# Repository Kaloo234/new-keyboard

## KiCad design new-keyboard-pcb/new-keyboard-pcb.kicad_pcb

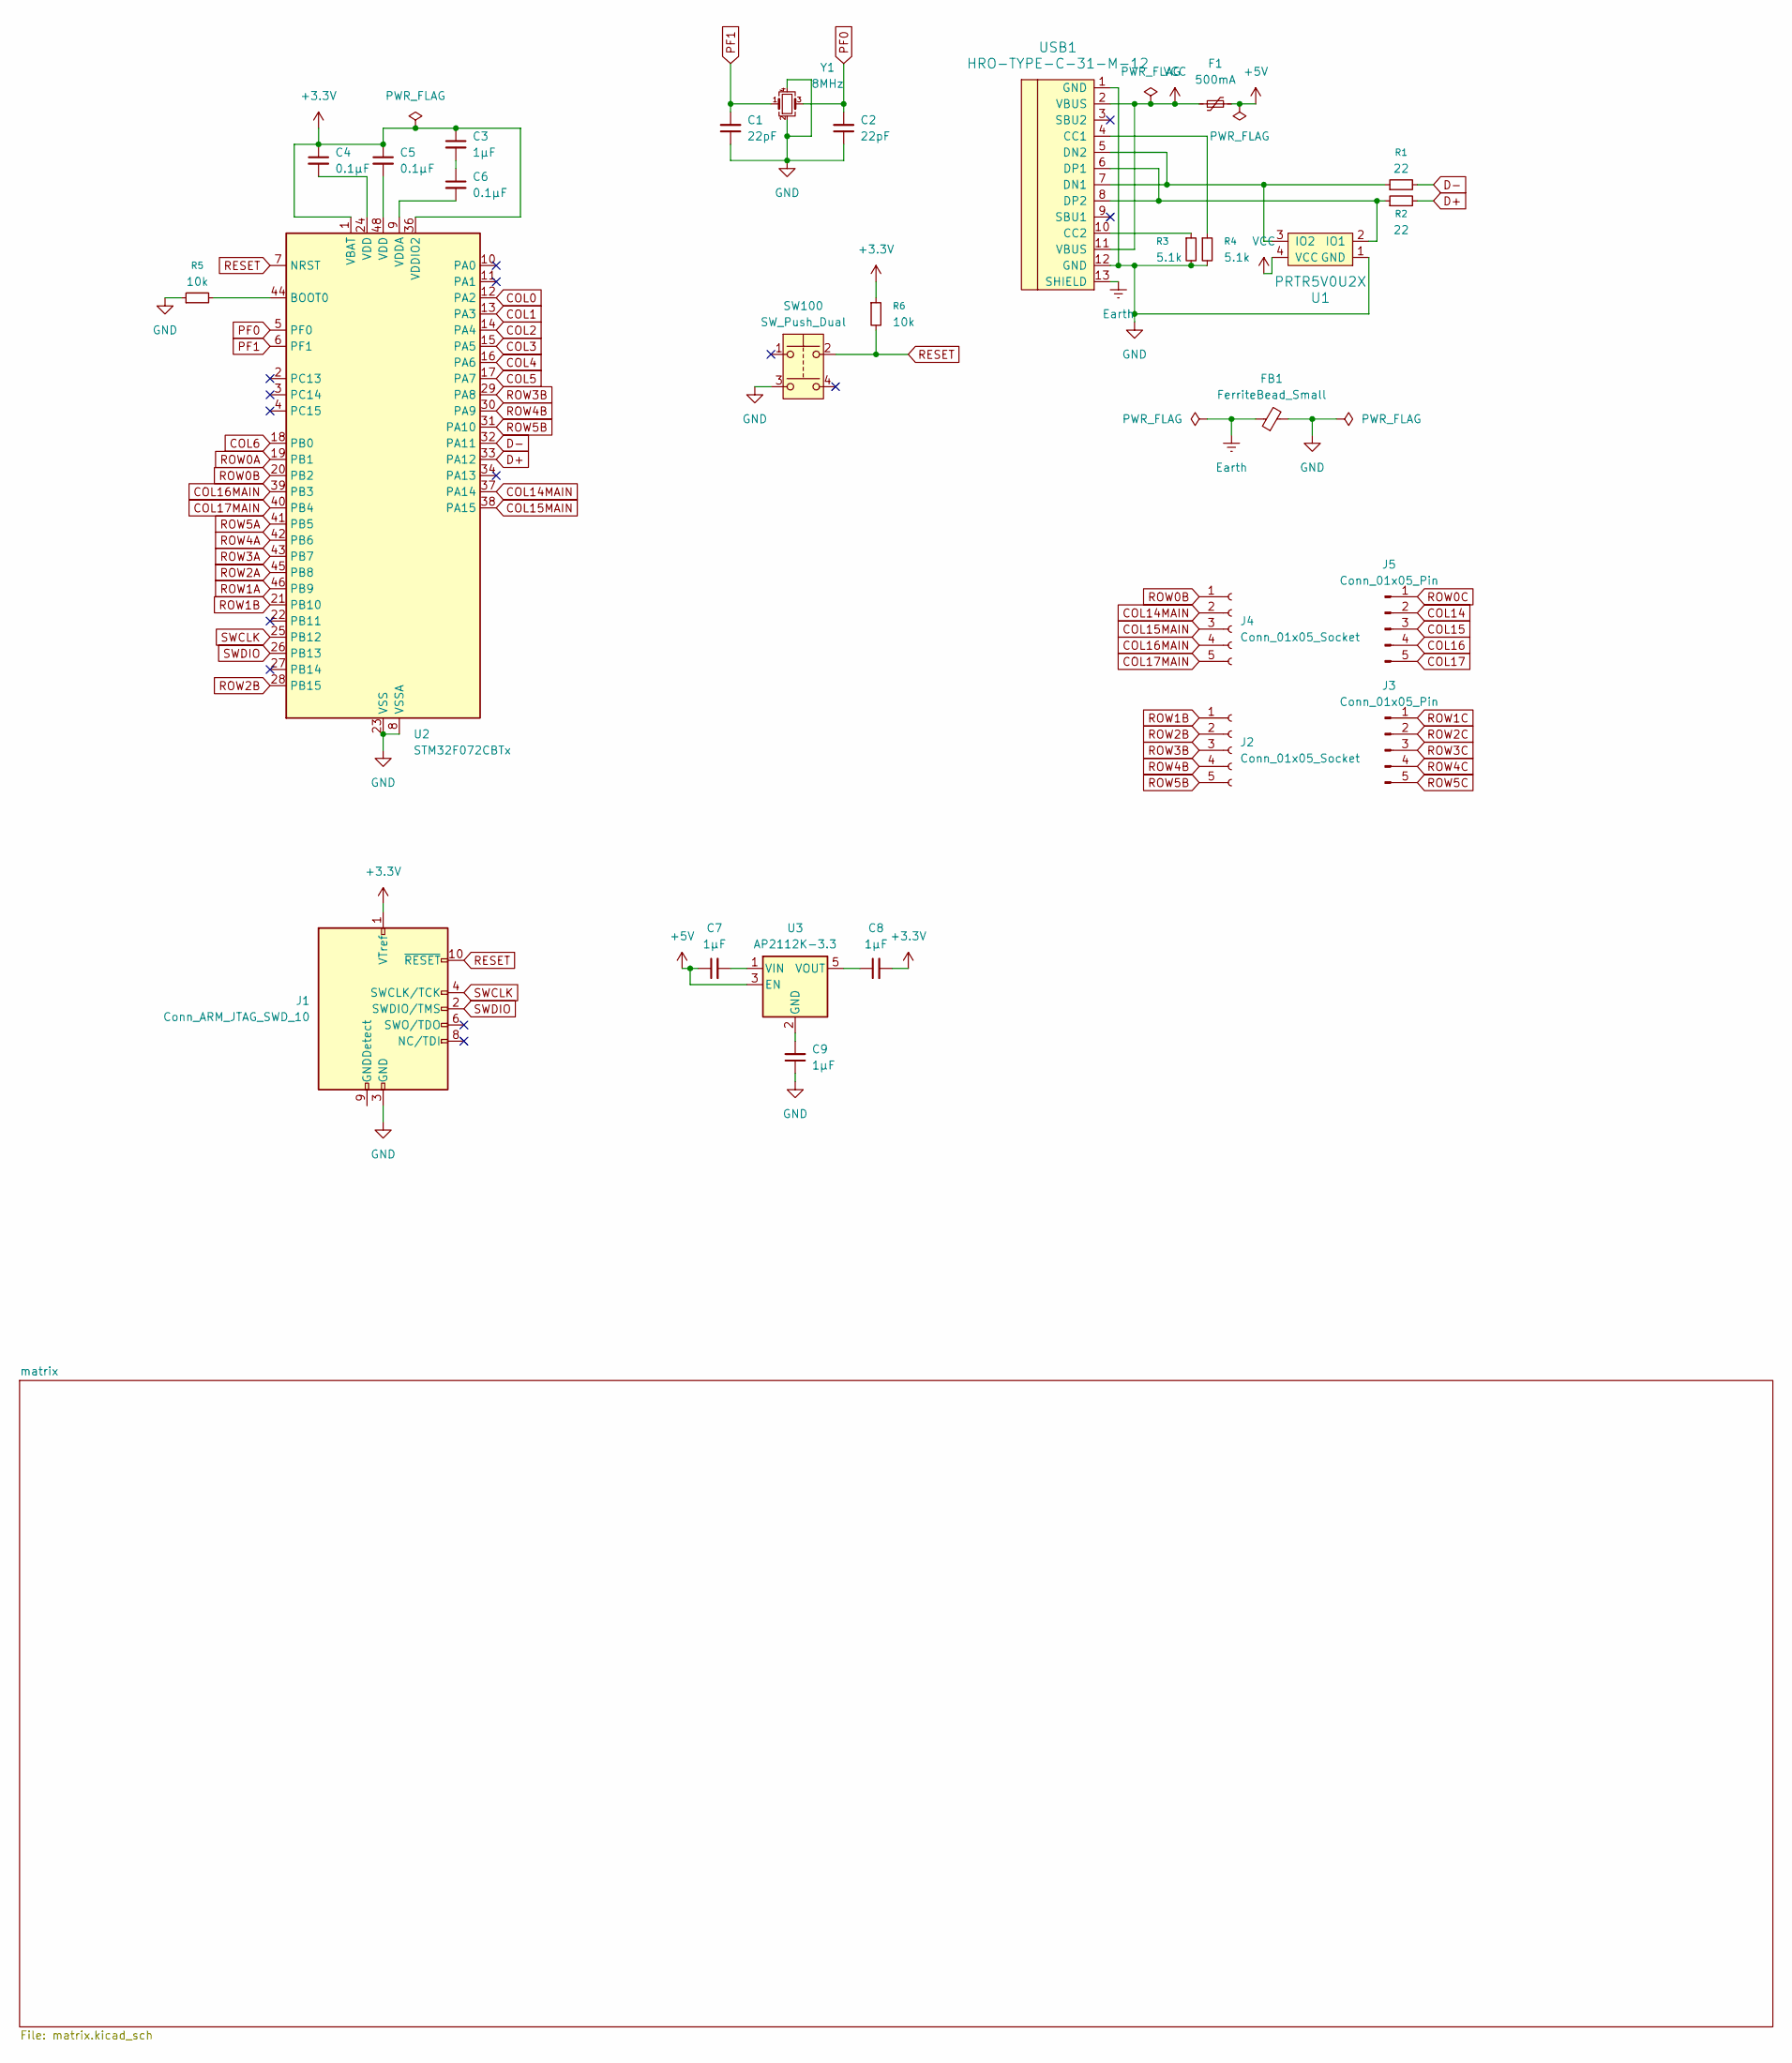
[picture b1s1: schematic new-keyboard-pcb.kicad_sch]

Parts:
C1, C2: 22pF; C_0805_2012Metric_Pad1.18x1.45mm_HandSolder
C3, C7, C8, C9: 1µF; C_0805_2012Metric_Pad1.18x1.45mm_HandSolder
C4, C5, C6: 0.1µF; C_0805_2012Metric_Pad1.18x1.45mm_HandSolder
F1: 500mA; Fuse_1206_3216Metric_Pad1.42x1.75mm_HandSolder
FB1: FerriteBead_Small; L_0805_2012Metric_Pad1.05x1.20mm_HandSolder
J1: Conn_ARM_JTAG_SWD_10; PinSocket_2x05_P2.54mm_Vertical
J2, J4: Conn_01x05_Socket; connector
J3, J5: Conn_01x05_Pin; connector
R1, R2: 22; R_0805_2012Metric_Pad1.20x1.40mm_HandSolder
R3, R4: 5.1k; R_0805_2012Metric_Pad1.20x1.40mm_HandSolder
R5, R6: 10k; R_0805_2012Metric_Pad1.20x1.40mm_HandSolder
SW100: SW_Push_Dual; SKQG-1155865
U1: PRTR5V0U2X; SOT143B
U2: STM32F072CBTx; LQFP-48_7x7mm_P0.5mm
U3: AP2112K-3.3; SOT-23-5
USB1: HRO-TYPE-C-31-M-12; HRO-TYPE-C-31-M-12-HandSoldering
Y1: 8MHz; Crystal_SMD_3225-4Pin_3.2x2.5mm_HandSoldering

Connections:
+3.3V: C3.1, C4.1, C5.1, C8.2, J1.1 (VTref), R6.1, U2.1 (VBAT), U2.36 (VDDIO2)
+5V: C7.1, F1.2, U3.3 (EN)
COL0: U2.12 (PA2); also elsewhere on the board
COL1: U2.13 (PA3); also elsewhere on the board
COL2: U2.14 (PA4); also elsewhere on the board
COL3: U2.15 (PA5); also elsewhere on the board
COL4: U2.16 (PA6); also elsewhere on the board
COL5: U2.17 (PA7); also elsewhere on the board
COL6: U2.18 (PB0); also elsewhere on the board
COL14: J5.2; also elsewhere on the board
COL14MAIN: J4.2, U2.37 (PA14)
COL15: J5.3; also elsewhere on the board
COL15MAIN: J4.3, U2.38 (PA15)
COL16: J5.4; also elsewhere on the board
COL16MAIN: J4.4, U2.39 (PB3)
COL17: J5.5; also elsewhere on the board
COL17MAIN: J4.5, U2.40 (PB4)
D+: R2.2, U2.33 (PA12)
D-: R1.2, U2.32 (PA11)
Earth: FB1.1, USB1.13 (SHIELD)
GND: C1.1, C2.1, C9.1, FB1.2, J1.3 (GND), J1.5 (GND), R3.2, R4.2, R5.1, SW100.3, U1.1 (GND), U2.8 (VSSA), U2.23 (VSS), U2.35 (VSS), U2.47 (VSS), USB1.1 (GND), USB1.12 (GND), Y1.2, Y1.4
unnamed: C3.2, C6.1
unnamed: C4.2, U2.24 (VDD)
unnamed: C5.2, U2.48 (VDD)
unnamed: R2.1, U1.2 (IO1), USB1.6 (DP1), USB1.8 (DP2)
unnamed: R1.1, U1.3 (IO2), USB1.5 (DN2), USB1.7 (DN1)
unnamed: R5.2, U2.44 (BOOT0)
unnamed: C6.2, U2.9 (VDDA)
unnamed: C9.2, U3.2 (GND)
unnamed: C7.2, U3.1 (VIN)
unnamed: C8.1, U3.5 (VOUT)
unnamed: R4.1, USB1.4 (CC1)
unnamed: R3.1, USB1.10 (CC2)
PF0: C2.2, U2.5 (PF0), Y1.3
PF1: C1.2, U2.6 (PF1), Y1.1
RESET: J1.10 (~RESET), R6.2, SW100.2, U2.7 (NRST)
ROW0A: U2.19 (PB1); also elsewhere on the board
ROW0B: J4.1, U2.20 (PB2); also elsewhere on the board
ROW0C: J5.1; also elsewhere on the board
ROW1A: U2.46 (PB9); also elsewhere on the board
ROW1B: J2.1, U2.21 (PB10); also elsewhere on the board
ROW1C: J3.1; also elsewhere on the board
ROW2A: U2.45 (PB8); also elsewhere on the board
ROW2B: J2.2, U2.28 (PB15); also elsewhere on the board
ROW2C: J3.2; also elsewhere on the board
ROW3A: U2.43 (PB7); also elsewhere on the board
ROW3B: J2.3, U2.29 (PA8); also elsewhere on the board
ROW3C: J3.3; also elsewhere on the board
ROW4A: U2.42 (PB6); also elsewhere on the board
ROW4B: J2.4, U2.30 (PA9); also elsewhere on the board
ROW4C: J3.4; also elsewhere on the board
ROW5A: U2.41 (PB5); also elsewhere on the board
ROW5B: J2.5, U2.31 (PA10); also elsewhere on the board
ROW5C: J3.5; also elsewhere on the board
SWCLK: J1.4 (SWCLK/TCK), U2.25 (PB12)
SWDIO: J1.2 (SWDIO/TMS), U2.26 (PB13)
VCC: F1.1, U1.4 (VCC), USB1.2 (VBUS), USB1.11 (VBUS)

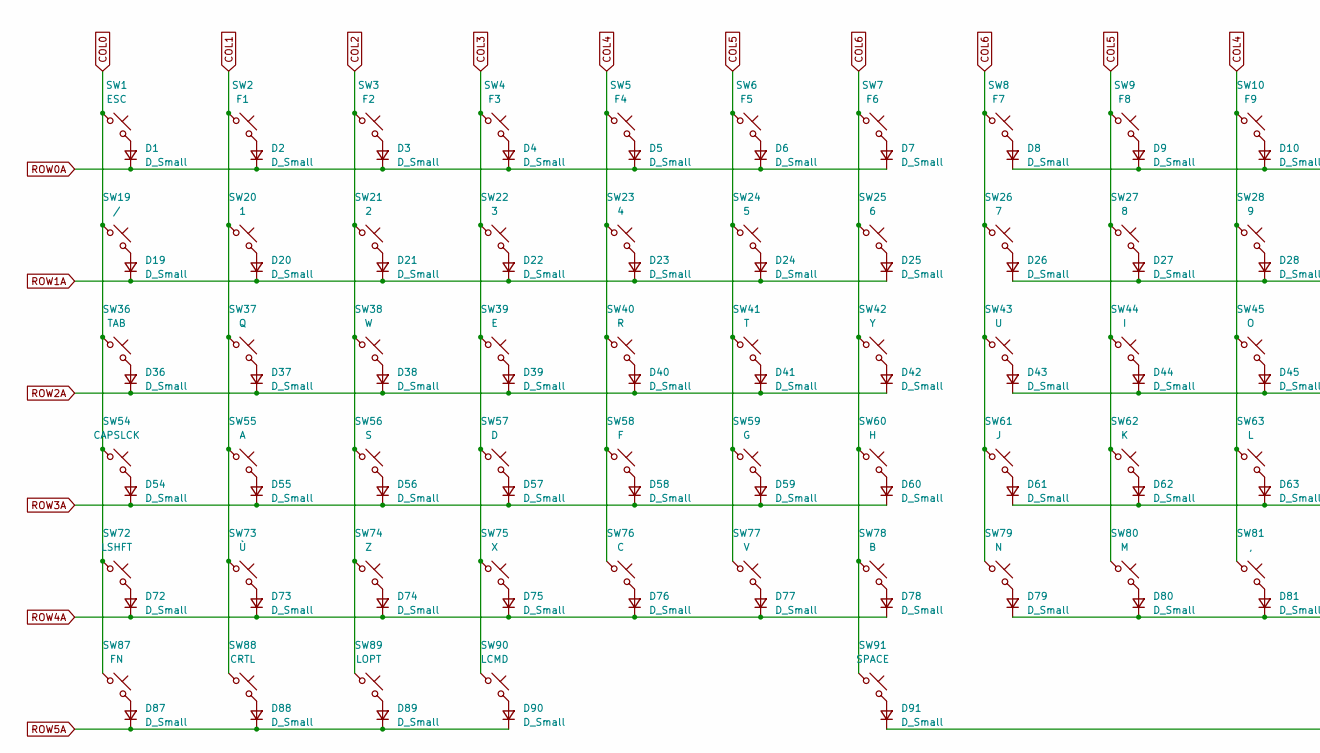
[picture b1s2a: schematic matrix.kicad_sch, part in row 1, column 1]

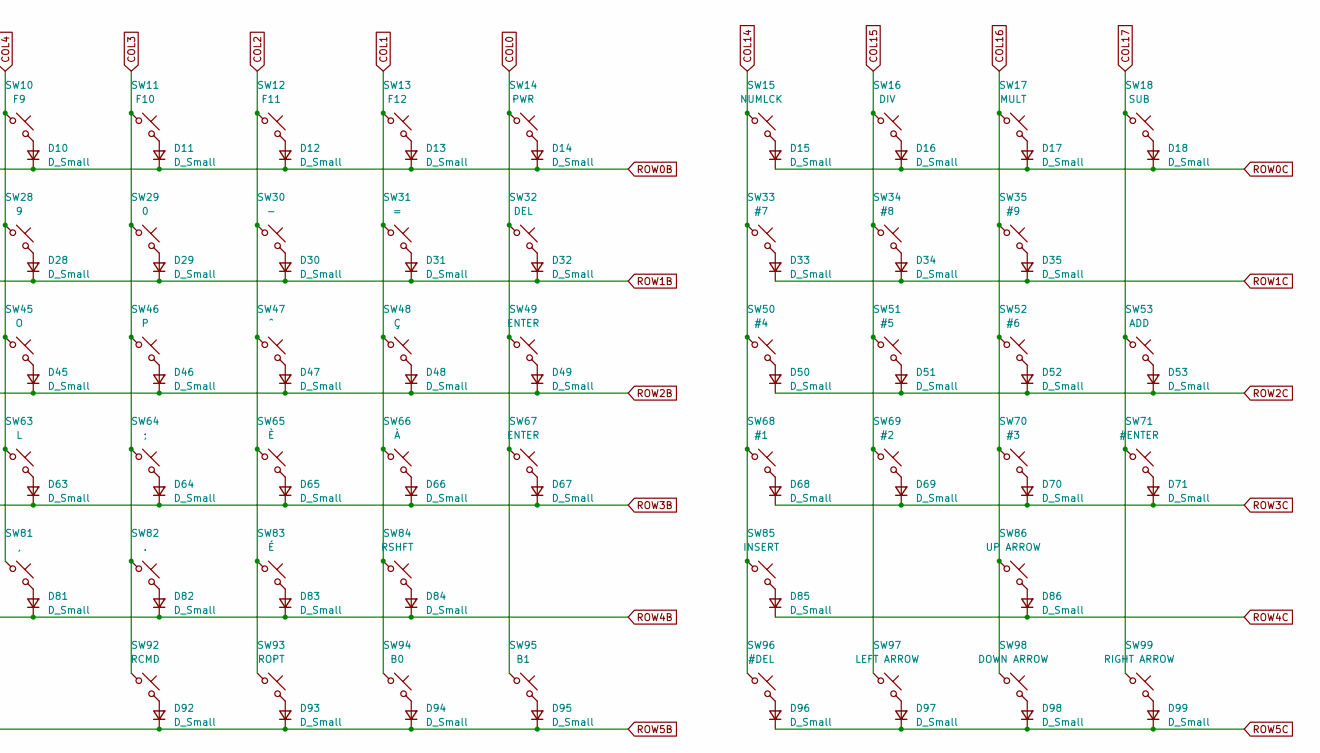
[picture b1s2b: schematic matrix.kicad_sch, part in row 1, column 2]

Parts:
D1, D2, D3, D4, D5, D6, D7, D8, D9, D10, D11, D12, D13, D14, D15, D16, D17, D18, D19, D20, D21, D22, D23, D24, D25, D26, D27, D28, D29, D30, D31, D32, D33, D34, D35, D36, D37, D38, D39, D40, D41, D42, D43, D44, D45, D46, D47, D48, D49, D50, D51, D52, D53, D54, D55, D56, D57, D58, D59, D60, D61, D62, D63, D64, D65, D66, D67, D68, D69, D70, D71, D72, D73, D74, D75, D76, D77, D78, D79, D80, D81, D82, D83, D84, D85, D86, D87, D88, D89, D90, D91, D92, D93, D94, D95, D96, D97, D98, D99: D_Small; D_0805_2012Metric_Pad1.15x1.40mm_HandSolder
SW1: ESC; Kailh-PG1353-Hotswap-1.5U
SW2: F1; Kailh-PG1353-Hotswap-1U
SW3: F2; Kailh-PG1353-Hotswap-1U
SW4: F3; Kailh-PG1353-Hotswap-1U
SW5: F4; Kailh-PG1353-Hotswap-1U
SW6: F5; Kailh-PG1353-Hotswap-1U
SW7: F6; Kailh-PG1353-Hotswap-1U
SW8: F7; Kailh-PG1353-Hotswap-1U
SW9: F8; Kailh-PG1353-Hotswap-1U
SW10: F9; Kailh-PG1353-Hotswap-1U
SW11: F10; Kailh-PG1353-Hotswap-1U
SW12: F11; Kailh-PG1353-Hotswap-1U
SW13: F12; Kailh-PG1353-Hotswap-1U
SW14: PWR; Kailh-PG1353-Hotswap-1.5U
SW15: NUMLCK; Kailh-PG1353-Hotswap-1U
SW16: DIV; Kailh-PG1353-Hotswap-1U
SW17: MULT; Kailh-PG1353-Hotswap-1U
SW18: SUB; Kailh-PG1353-Hotswap-1U
SW19: /; Kailh-PG1353-Hotswap-1U
SW20: 1; Kailh-PG1353-Hotswap-1U
SW21: 2; Kailh-PG1353-Hotswap-1U
SW22: 3; Kailh-PG1353-Hotswap-1U
SW23: 4; Kailh-PG1353-Hotswap-1U
SW24: 5; Kailh-PG1353-Hotswap-1U
SW25: 6; Kailh-PG1353-Hotswap-1U
SW26: 7; Kailh-PG1353-Hotswap-1U
SW27: 8; Kailh-PG1353-Hotswap-1U
SW28: 9; Kailh-PG1353-Hotswap-1U
SW29: 0; Kailh-PG1353-Hotswap-1U
SW30: -; Kailh-PG1353-Hotswap-1U
SW31: =; Kailh-PG1353-Hotswap-1U
SW32: DEL; Kailh-PG1353-Hotswap-2U
SW33: #7; Kailh-PG1353-Hotswap-1U
SW34: #8; Kailh-PG1353-Hotswap-1U
SW35: #9; Kailh-PG1353-Hotswap-1U
SW36: TAB; Kailh-PG1353-Hotswap-1.5U
SW37: Q; Kailh-PG1353-Hotswap-1U
SW38: W; Kailh-PG1353-Hotswap-1U
SW39: E; Kailh-PG1353-Hotswap-1U
SW40: R; Kailh-PG1353-Hotswap-1U
SW41: T; Kailh-PG1353-Hotswap-1U
SW42: Y; Kailh-PG1353-Hotswap-1U
SW43: U; Kailh-PG1353-Hotswap-1U
SW44: I; Kailh-PG1353-Hotswap-1U
SW45: O; Kailh-PG1353-Hotswap-1U
SW46: P; Kailh-PG1353-Hotswap-1U
SW47: ^; Kailh-PG1353-Hotswap-1U
SW48: Ç; Kailh-PG1353-Hotswap-1U
SW49: ENTER; Kailh-PG1353-Hotswap-1.5U
SW50: #4; Kailh-PG1353-Hotswap-1U
SW51: #5; Kailh-PG1353-Hotswap-1U
SW52: #6; Kailh-PG1353-Hotswap-1U
SW53: ADD; Kailh-PG1353-Hotswap-2U
SW54: CAPSLCK; Kailh-PG1353-Hotswap-1.75U
SW55: A; Kailh-PG1353-Hotswap-1U
SW56: S; Kailh-PG1353-Hotswap-1U
SW57: D; Kailh-PG1353-Hotswap-1U
SW58: F; Kailh-PG1353-Hotswap-1U
SW59: G; Kailh-PG1353-Hotswap-1U
SW60: H; Kailh-PG1353-Hotswap-1U
SW61: J; Kailh-PG1353-Hotswap-1U
SW62: K; Kailh-PG1353-Hotswap-1U
SW63: L; Kailh-PG1353-Hotswap-1U
SW64: ;; Kailh-PG1353-Hotswap-1U
SW65: È; Kailh-PG1353-Hotswap-1U
SW66: À; Kailh-PG1353-Hotswap-1U
SW67: ENTER; Kailh-PG1353-Hotswap-1.25U
SW68: #1; Kailh-PG1353-Hotswap-1U
SW69: #2; Kailh-PG1353-Hotswap-1U
SW70: #3; Kailh-PG1353-Hotswap-1U
SW71: #ENTER; Kailh-PG1353-Hotswap-2U
SW72: LSHFT; Kailh-PG1353-Hotswap-1.25U
SW73: Ù; Kailh-PG1353-Hotswap-1U
SW74: Z; Kailh-PG1353-Hotswap-1U
SW75: X; Kailh-PG1353-Hotswap-1U
SW76: C; Kailh-PG1353-Hotswap-1U
SW77: V; Kailh-PG1353-Hotswap-1U
SW78: B; Kailh-PG1353-Hotswap-1U
SW79: N; Kailh-PG1353-Hotswap-1U
SW80: M; Kailh-PG1353-Hotswap-1U
SW81: ,; Kailh-PG1353-Hotswap-1U
SW82: .; Kailh-PG1353-Hotswap-1U
SW83: É; Kailh-PG1353-Hotswap-1U
SW84: RSHFT; Kailh-PG1353-Hotswap-2.75U
SW85: INSERT; Kailh-PG1353-Hotswap-2U
SW86: UP ARROW; Kailh-PG1353-Hotswap-1U
SW87: FN; Kailh-PG1353-Hotswap-1U
SW88: CRTL; Kailh-PG1353-Hotswap-1U
SW89: LOPT; Kailh-PG1353-Hotswap-1U
SW90: LCMD; Kailh-PG1353-Hotswap-1.25U
SW91: SPACE; Kailh-PG1353-Hotswap-6.25U
SW92: RCMD; Kailh-PG1353-Hotswap-1.25U
SW93: ROPT; Kailh-PG1353-Hotswap-1U
SW94: B0; Kailh-PG1353-Hotswap-1.25U
SW95: B1; Kailh-PG1353-Hotswap-1U
SW96: #DEL; Kailh-PG1353-Hotswap-1U
SW97: LEFT ARROW; Kailh-PG1353-Hotswap-1U
SW98: DOWN ARROW; Kailh-PG1353-Hotswap-1U
SW99: RIGHT ARROW; Kailh-PG1353-Hotswap-1U

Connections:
COL0: SW1.1, SW14.1, SW19.1, SW32.1, SW36.1, SW49.1, SW54.1, SW67.1, SW72.1, SW87.1, SW95.1; also elsewhere on the board
COL1: SW2.1, SW13.1, SW20.1, SW31.1, SW37.1, SW48.1, SW55.1, SW66.1, SW73.1, SW84.1, SW88.1, SW94.1; also elsewhere on the board
COL2: SW3.1, SW12.1, SW21.1, SW30.1, SW38.1, SW47.1, SW56.1, SW65.1, SW74.1, SW83.1, SW89.1, SW93.1; also elsewhere on the board
COL3: SW4.1, SW11.1, SW22.1, SW29.1, SW39.1, SW46.1, SW57.1, SW64.1, SW75.1, SW82.1, SW90.1, SW92.1; also elsewhere on the board
COL4: SW5.1, SW10.1, SW23.1, SW28.1, SW40.1, SW45.1, SW58.1, SW63.1, SW76.1, SW81.1; also elsewhere on the board
COL5: SW6.1, SW9.1, SW24.1, SW27.1, SW41.1, SW44.1, SW59.1, SW62.1, SW77.1, SW80.1; also elsewhere on the board
COL6: SW7.1, SW8.1, SW25.1, SW26.1, SW42.1, SW43.1, SW60.1, SW61.1, SW78.1, SW79.1, SW91.1; also elsewhere on the board
COL14: SW15.1, SW33.1, SW50.1, SW68.1, SW85.1, SW96.1; also elsewhere on the board
COL15: SW16.1, SW34.1, SW51.1, SW69.1, SW97.1; also elsewhere on the board
COL16: SW17.1, SW35.1, SW52.1, SW70.1, SW86.1, SW98.1; also elsewhere on the board
COL17: SW18.1, SW53.1, SW71.1, SW99.1; also elsewhere on the board
unnamed: D1.2 (A), SW1.2
unnamed: D2.2 (A), SW2.2
unnamed: D3.2 (A), SW3.2
unnamed: D4.2 (A), SW4.2
unnamed: D5.2 (A), SW5.2
unnamed: D6.2 (A), SW6.2
unnamed: D7.2 (A), SW7.2
unnamed: D8.2 (A), SW8.2
unnamed: D9.2 (A), SW9.2
unnamed: D10.2 (A), SW10.2
unnamed: D11.2 (A), SW11.2
unnamed: D12.2 (A), SW12.2
unnamed: D13.2 (A), SW13.2
unnamed: D14.2 (A), SW14.2
unnamed: D15.2 (A), SW15.2
unnamed: D16.2 (A), SW16.2
unnamed: D17.2 (A), SW17.2
unnamed: D18.2 (A), SW18.2
unnamed: D19.2 (A), SW19.2
unnamed: D20.2 (A), SW20.2
unnamed: D21.2 (A), SW21.2
unnamed: D22.2 (A), SW22.2
unnamed: D23.2 (A), SW23.2
unnamed: D24.2 (A), SW24.2
unnamed: D25.2 (A), SW25.2
unnamed: D26.2 (A), SW26.2
unnamed: D27.2 (A), SW27.2
unnamed: D28.2 (A), SW28.2
unnamed: D29.2 (A), SW29.2
unnamed: D30.2 (A), SW30.2
unnamed: D31.2 (A), SW31.2
unnamed: D32.2 (A), SW32.2
unnamed: D33.2 (A), SW33.2
unnamed: D34.2 (A), SW34.2
unnamed: D35.2 (A), SW35.2
unnamed: D36.2 (A), SW36.2
unnamed: D37.2 (A), SW37.2
unnamed: D38.2 (A), SW38.2
unnamed: D39.2 (A), SW39.2
unnamed: D40.2 (A), SW40.2
unnamed: D41.2 (A), SW41.2
unnamed: D42.2 (A), SW42.2
unnamed: D43.2 (A), SW43.2
unnamed: D44.2 (A), SW44.2
unnamed: D45.2 (A), SW45.2
unnamed: D46.2 (A), SW46.2
unnamed: D47.2 (A), SW47.2
unnamed: D48.2 (A), SW48.2
unnamed: D49.2 (A), SW49.2
unnamed: D50.2 (A), SW50.2
unnamed: D51.2 (A), SW51.2
unnamed: D52.2 (A), SW52.2
unnamed: D53.2 (A), SW53.2
unnamed: D54.2 (A), SW54.2
unnamed: D55.2 (A), SW55.2
unnamed: D56.2 (A), SW56.2
unnamed: D57.2 (A), SW57.2
unnamed: D58.2 (A), SW58.2
unnamed: D59.2 (A), SW59.2
unnamed: D60.2 (A), SW60.2
unnamed: D61.2 (A), SW61.2
unnamed: D62.2 (A), SW62.2
unnamed: D63.2 (A), SW63.2
unnamed: D64.2 (A), SW64.2
unnamed: D65.2 (A), SW65.2
unnamed: D66.2 (A), SW66.2
unnamed: D67.2 (A), SW67.2
unnamed: D68.2 (A), SW68.2
unnamed: D69.2 (A), SW69.2
unnamed: D70.2 (A), SW70.2
unnamed: D71.2 (A), SW71.2
unnamed: D72.2 (A), SW72.2
unnamed: D73.2 (A), SW73.2
unnamed: D74.2 (A), SW74.2
unnamed: D75.2 (A), SW75.2
unnamed: D76.2 (A), SW76.2
unnamed: D77.2 (A), SW77.2
unnamed: D78.2 (A), SW78.2
unnamed: D79.2 (A), SW79.2
unnamed: D80.2 (A), SW80.2
unnamed: D81.2 (A), SW81.2
unnamed: D82.2 (A), SW82.2
unnamed: D83.2 (A), SW83.2
unnamed: D84.2 (A), SW84.2
unnamed: D85.2 (A), SW85.2
unnamed: D86.2 (A), SW86.2
unnamed: D87.2 (A), SW87.2
unnamed: D88.2 (A), SW88.2
unnamed: D89.2 (A), SW89.2
unnamed: D90.2 (A), SW90.2
unnamed: D91.2 (A), SW91.2
unnamed: D92.2 (A), SW92.2
unnamed: D93.2 (A), SW93.2
unnamed: D94.2 (A), SW94.2
unnamed: D95.2 (A), SW95.2
unnamed: D96.2 (A), SW96.2
unnamed: D97.2 (A), SW97.2
unnamed: D98.2 (A), SW98.2
unnamed: D99.2 (A), SW99.2
ROW0A: D1.1 (K), D2.1 (K), D3.1 (K), D4.1 (K), D5.1 (K), D6.1 (K), D7.1 (K); also elsewhere on the board
ROW0B: D8.1 (K), D9.1 (K), D10.1 (K), D11.1 (K), D12.1 (K), D13.1 (K), D14.1 (K); also elsewhere on the board
ROW0C: D15.1 (K), D16.1 (K), D17.1 (K), D18.1 (K); also elsewhere on the board
ROW1A: D19.1 (K), D20.1 (K), D21.1 (K), D22.1 (K), D23.1 (K), D24.1 (K), D25.1 (K); also elsewhere on the board
ROW1B: D26.1 (K), D27.1 (K), D28.1 (K), D29.1 (K), D30.1 (K), D31.1 (K), D32.1 (K); also elsewhere on the board
ROW1C: D33.1 (K), D34.1 (K), D35.1 (K); also elsewhere on the board
ROW2A: D36.1 (K), D37.1 (K), D38.1 (K), D39.1 (K), D40.1 (K), D41.1 (K), D42.1 (K); also elsewhere on the board
ROW2B: D43.1 (K), D44.1 (K), D45.1 (K), D46.1 (K), D47.1 (K), D48.1 (K), D49.1 (K); also elsewhere on the board
ROW2C: D50.1 (K), D51.1 (K), D52.1 (K), D53.1 (K); also elsewhere on the board
ROW3A: D54.1 (K), D55.1 (K), D56.1 (K), D57.1 (K), D58.1 (K), D59.1 (K), D60.1 (K); also elsewhere on the board
ROW3B: D61.1 (K), D62.1 (K), D63.1 (K), D64.1 (K), D65.1 (K), D66.1 (K), D67.1 (K); also elsewhere on the board
ROW3C: D68.1 (K), D69.1 (K), D70.1 (K), D71.1 (K); also elsewhere on the board
ROW4A: D72.1 (K), D73.1 (K), D74.1 (K), D75.1 (K), D76.1 (K), D77.1 (K), D78.1 (K); also elsewhere on the board
ROW4B: D79.1 (K), D80.1 (K), D81.1 (K), D82.1 (K), D83.1 (K), D84.1 (K); also elsewhere on the board
ROW4C: D85.1 (K), D86.1 (K); also elsewhere on the board
ROW5A: D87.1 (K), D88.1 (K), D89.1 (K), D90.1 (K); also elsewhere on the board
ROW5B: D91.1 (K), D92.1 (K), D93.1 (K), D94.1 (K), D95.1 (K); also elsewhere on the board
ROW5C: D96.1 (K), D97.1 (K), D98.1 (K), D99.1 (K); also elsewhere on the board

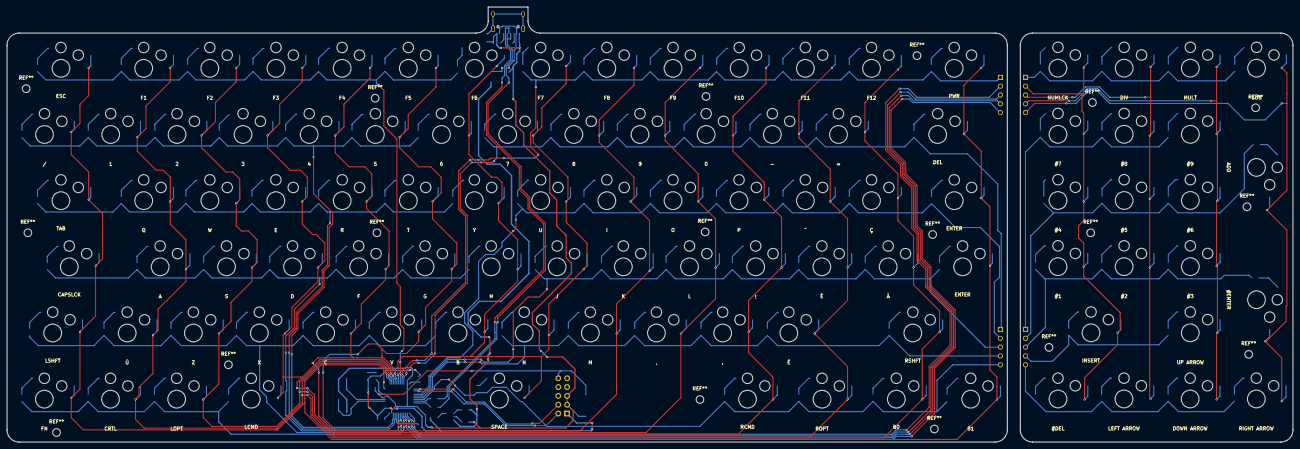
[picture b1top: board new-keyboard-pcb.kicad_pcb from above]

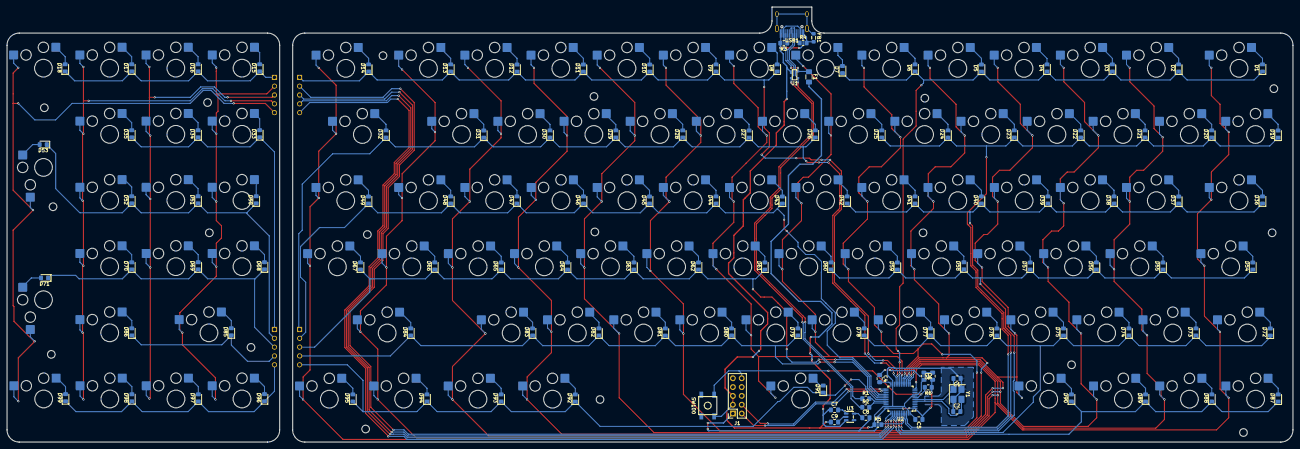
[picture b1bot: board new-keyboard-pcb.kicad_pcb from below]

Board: 2 copper layers, 370.2 x 125.2 mm, 226 parts (222 on the bottom side), 156 nets.

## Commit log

2026-04-02 schematic done
2026-04-02 routing done
2026-04-03 return to masterzen
2026-04-03 main keyboard switch placed
2026-04-03 numpad diodes placed
2026-04-03 all diodes placed
2026-04-03 other components placed + contours
2026-04-05 midway correcting hotswap sockets
2026-04-05 1/3 of matrix re-routed
2026-04-05 new connectors placed
2026-04-05 everything routed (again)
2026-04-05 pcb completed
2026-04-05 gerber output
2026-04-06 Correcting pogo connector connexions
2026-04-06 added mounting holes
2026-04-06 modified mounting holes and re-outputed
2026-04-06 create case
2026-04-06 added pogo conn holes
2026-04-24 big update
